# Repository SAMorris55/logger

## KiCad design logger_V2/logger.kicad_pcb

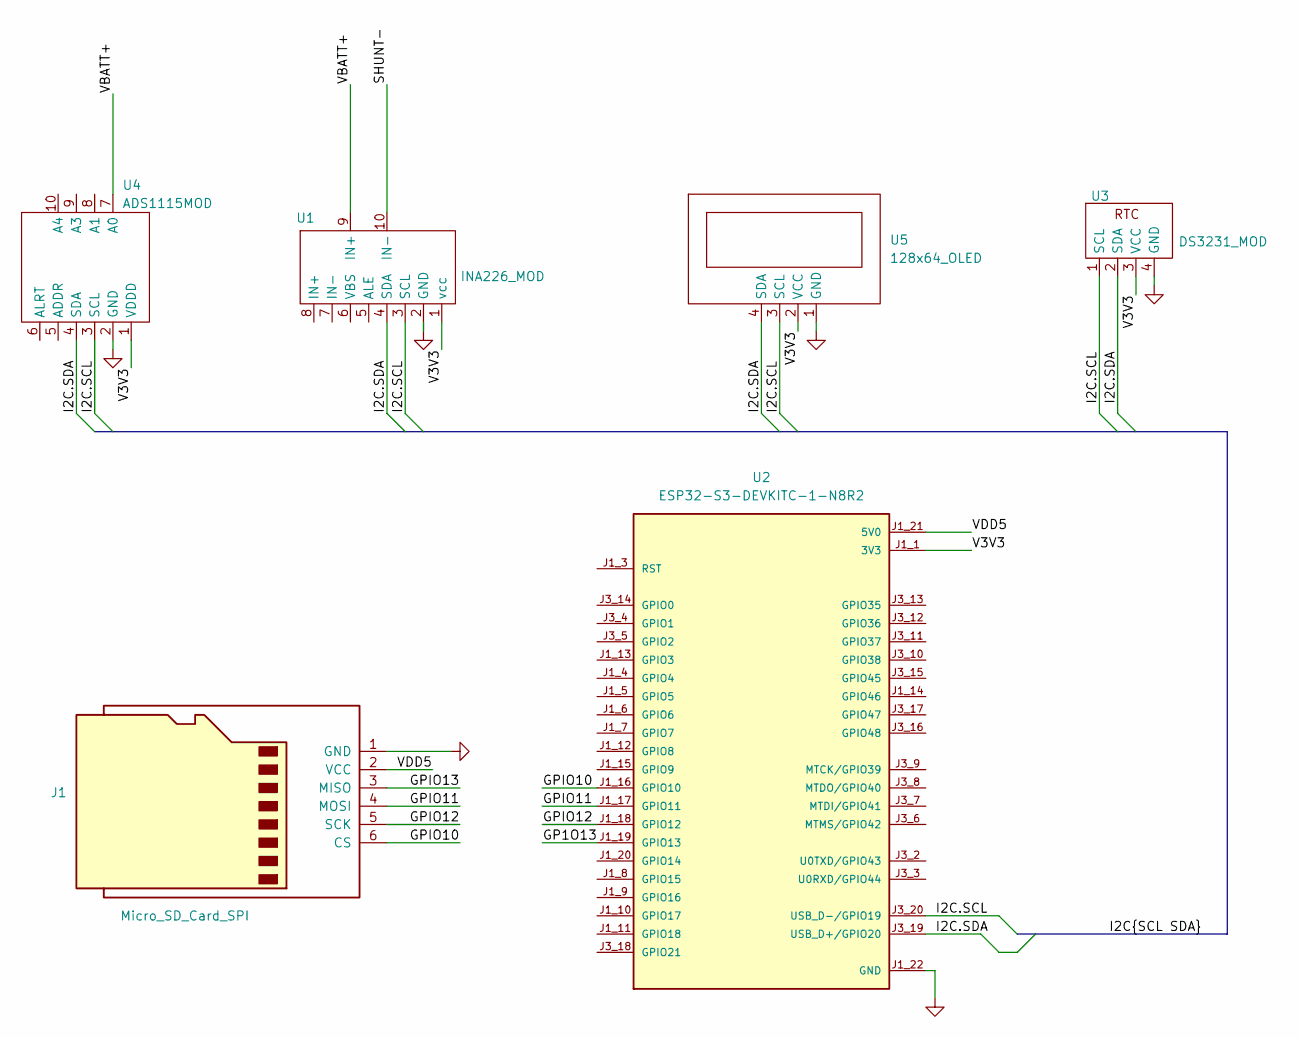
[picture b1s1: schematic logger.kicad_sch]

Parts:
J1: Micro_SD_Card_SPI; SD_CARD_MOD
U1: INA226_MOD; INA226MOD
U2: ESP32-S3-DEVKITC-1-N8R2; XCVR_ESP32-S3-DEVKITC-1-N8R2; PARTREV V1
U3: DS3231_MOD; rtc_DS3231_mod
U4: ADS1115MOD; ADS1015MOD
U5: 128x64_OLED; 0.96OLED

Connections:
3V3: U1.1 (vcc), U2.J1_1 (3V3), U2.J1_2 (3V3), U3.3 (VCC), U4.1 (VDDD), U5.2 (VCC)
/GP1O13: U2.J1_19 (GPIO13)
/GPIO10: J1.6 (CS), U2.J1_16 (GPIO10)
/GPIO11: J1.4 (MOSI), U2.J1_17 (GPIO11)
/GPIO12: J1.5 (SCK), U2.J1_18 (GPIO12)
/GPIO13: J1.3 (MISO)
/I2C.SCL: U1.3 (SCL), U2.J3_20 (USB_D-/GPIO19), U3.1 (SCL), U4.3 (SCL), U5.3 (SCL)
/I2C.SDA: U1.4 (SDA), U2.J3_19 (USB_D+/GPIO20), U3.2 (SDA), U4.4 (SDA), U5.4 (SDA)
/SHUNT-: U1.10 (IN-)
/VBATT+: U1.9 (IN+), U4.7 (A0)
/VDD5: J1.2 (VCC), U2.J1_21 (5V0)
GND: J1.1 (GND), U1.2 (GND), U2.J1_22 (GND), U2.J3_1 (GND), U2.J3_21 (GND), U2.J3_22 (GND), U3.4 (GND), U4.2 (GND), U5.1 (GND)

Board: 2 copper layers, 6 parts (0 on the bottom side), 9 nets, no tracks yet.

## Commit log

2026-03-19 Initial commit logger project
2026-03-19 deleted oversize photos files
